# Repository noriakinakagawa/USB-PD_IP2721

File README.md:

# USB-PD_IP2721
USB PDから5,15,20V3Aを選択して出力できる基板データ。

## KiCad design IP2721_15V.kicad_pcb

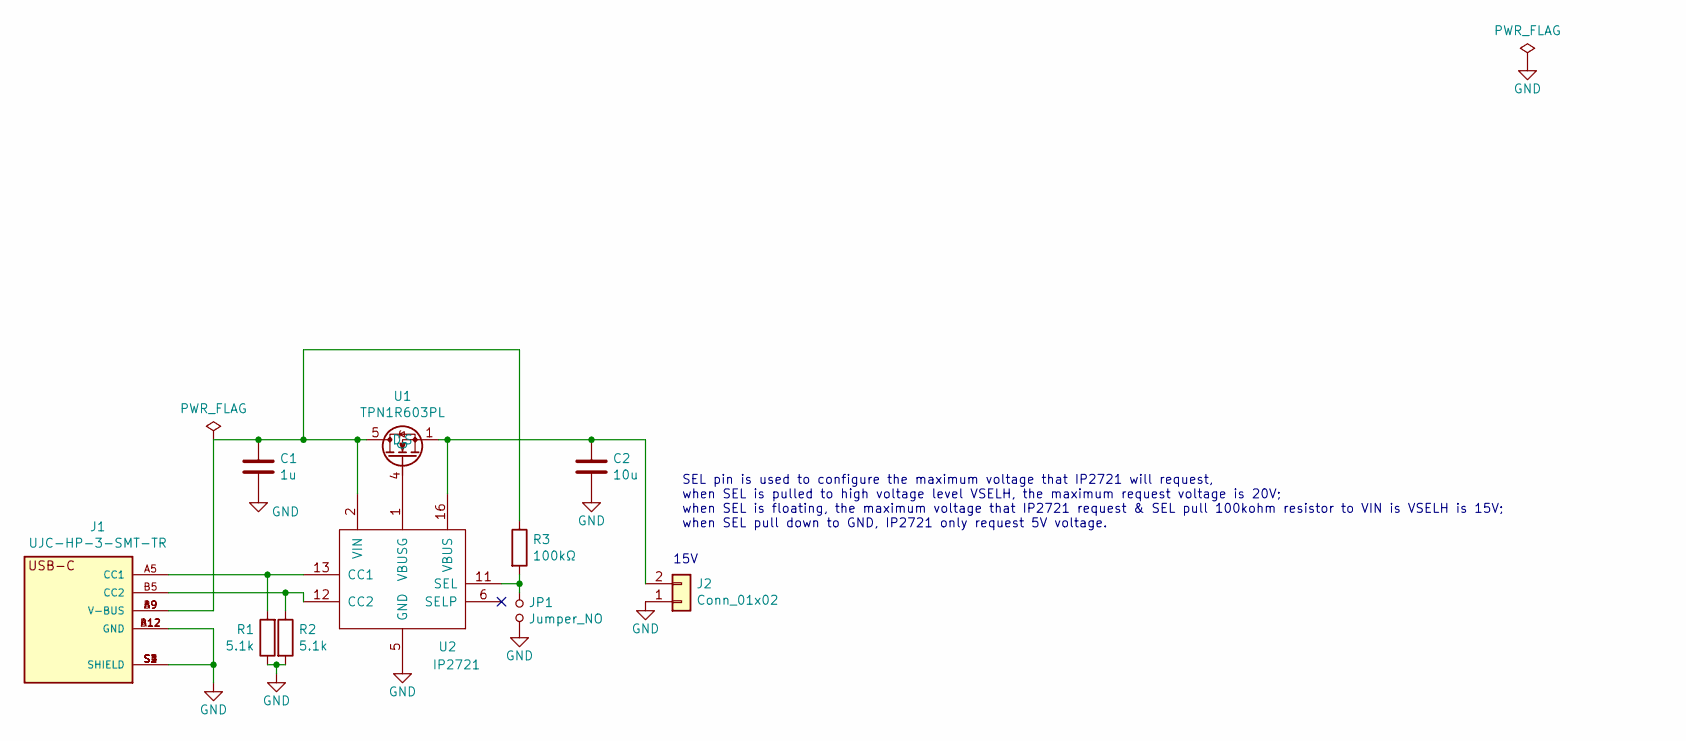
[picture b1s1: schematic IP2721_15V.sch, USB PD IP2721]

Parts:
C1: 1u; C_0603
C2: 10u; C_0603
J1: UJC-HP-3-SMT-TR; CUI_UJC-HP-3-SMT-TR
J2: Conn_01x02; Pin_Header_Straight_1x02_Pitch2.54mm
JP1: Jumper_NO; SolderJumper-2_P1.3mm_Open_RoundedPad1.0x1.5mm
R1, R2: 5.1k; R_0603
R3: 100kΩ; C_0603
U1: TPN1R603PL
U2: IP2721; TSSOP-16_4.4x5mm_Pitch0.65mm

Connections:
GND: C1.2, C2.2, J1.A12 (GND), J1.B12 (GND), J1.S1 (SHIELD), J1.S2 (SHIELD), J1.S3 (SHIELD), J1.S4 (SHIELD), J2.1, JP1.2, R1.1, R2.2, U2.5 (GND)
unnamed: C1.1, J1.A9 (V-BUS), J1.B9 (V-BUS), R3.1, U1.5 (D), U1.6 (D), U1.7 (D), U1.8 (D), U2.2 (VIN)
unnamed: C2.1, J2.2, U1.1 (S), U1.2 (S), U1.3 (S), U2.16 (VBUS)
unnamed: J1.A5 (CC1), R1.2, U2.13 (CC1)
unnamed: J1.B5 (CC2), R2.1, U2.12 (CC2)
unnamed: JP1.1, R3.2, U2.11 (SEL)
unnamed: U1.4 (G), U2.1 (VBUSG)

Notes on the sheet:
SEL pin is used to configure the maximum voltage that IP2721 will request, when SEL is pulled to high voltage level VSELH, the maximum request voltage is 20V; when SEL is floating, the maximum voltage that IP2721 request & SEL pull 100kohm resistor to VIN is VSELH is 15V; when SEL pull down to GND,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
15V

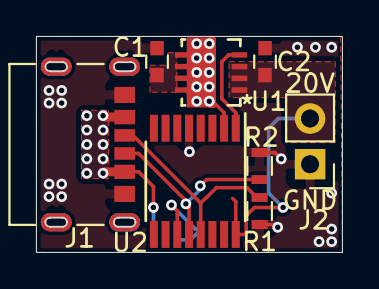
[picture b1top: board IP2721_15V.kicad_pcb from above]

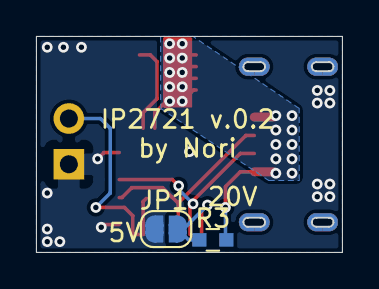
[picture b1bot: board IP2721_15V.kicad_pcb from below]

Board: 2 copper layers, 16.9 x 12.0 mm, 10 parts (2 on the bottom side), 7 nets.
